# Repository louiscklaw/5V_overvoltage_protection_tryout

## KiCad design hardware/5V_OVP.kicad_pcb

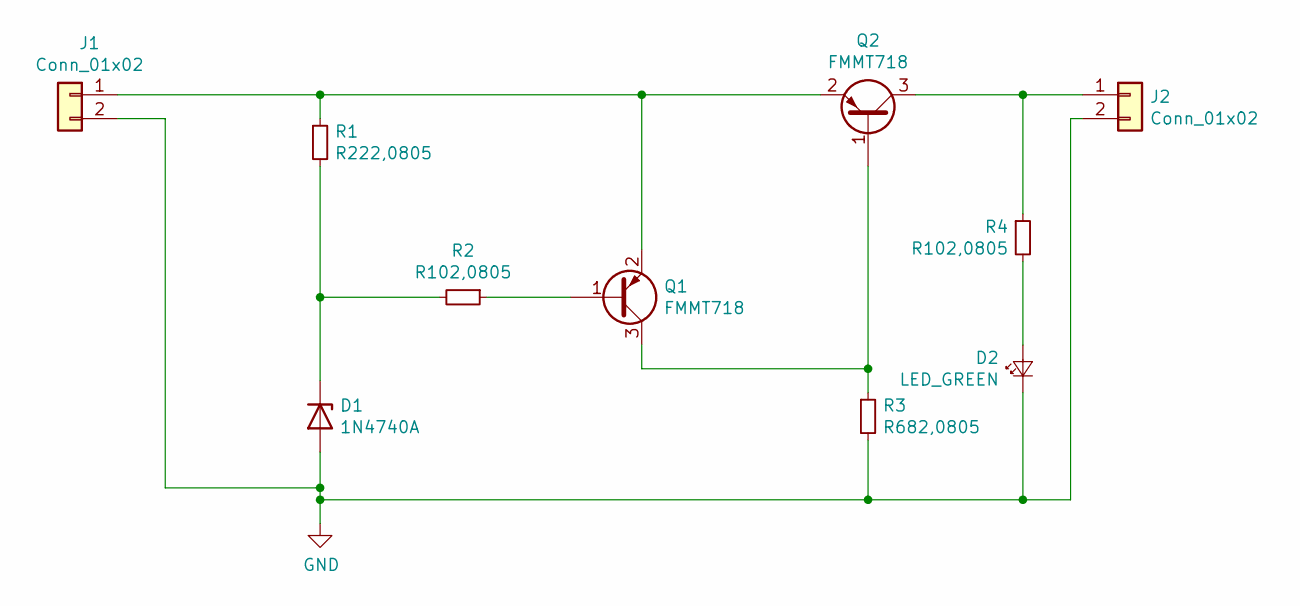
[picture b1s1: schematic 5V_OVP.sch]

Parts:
D1: 1N4740A; D_0805_2012Metric
D2: LED_GREEN; D_0805_2012Metric
J1, J2: Conn_01x02; PinHeader_1x02_P2.54mm_Vertical
Q1, Q2: FMMT718
R1: R222,0805; R_0805_2012Metric_Pad1.20x1.40mm_HandSolder
R2, R4: R102,0805; R_0805_2012Metric_Pad1.20x1.40mm_HandSolder
R3: R682,0805; R_0805_2012Metric_Pad1.20x1.40mm_HandSolder

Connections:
GND: D1.2 (A), D2.1 (K), J1.2, J2.2, R3.2
unnamed: D1.1 (K), R1.2, R2.2
unnamed: D2.2 (A), R4.2
unnamed: J1.1, Q1.2 (E), Q2.2 (E), R1.1
unnamed: J2.1, Q2.3 (C), R4.1
unnamed: Q1.1 (B), R2.1
unnamed: Q1.3 (C), Q2.1 (B), R3.1

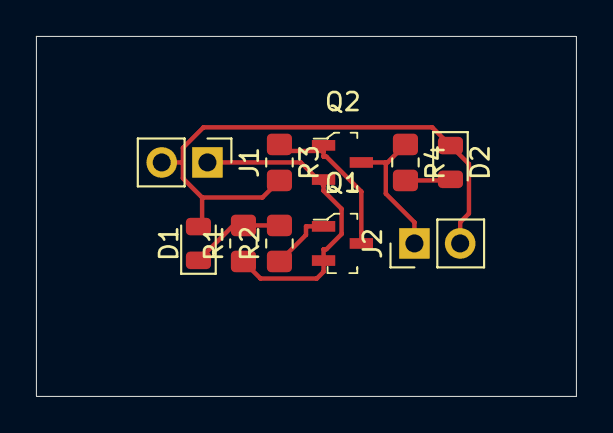
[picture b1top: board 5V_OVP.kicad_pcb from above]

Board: 2 copper layers, 30.0 x 20.0 mm, 10 parts (0 on the bottom side), 7 nets.

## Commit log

2021-10-02 update test,
